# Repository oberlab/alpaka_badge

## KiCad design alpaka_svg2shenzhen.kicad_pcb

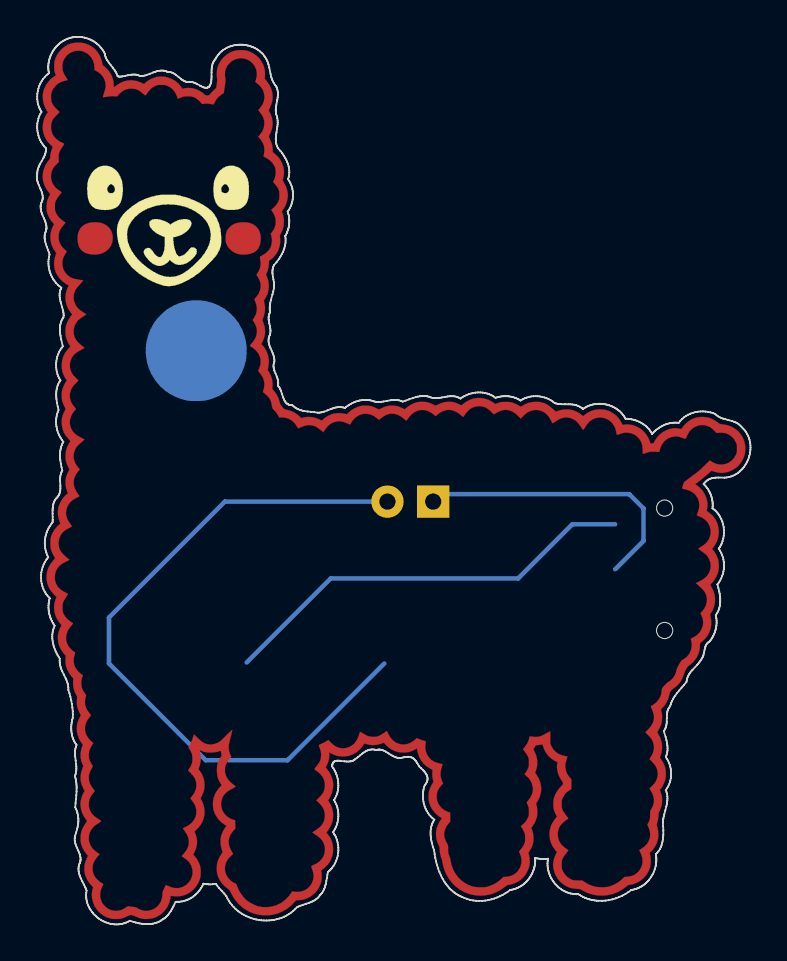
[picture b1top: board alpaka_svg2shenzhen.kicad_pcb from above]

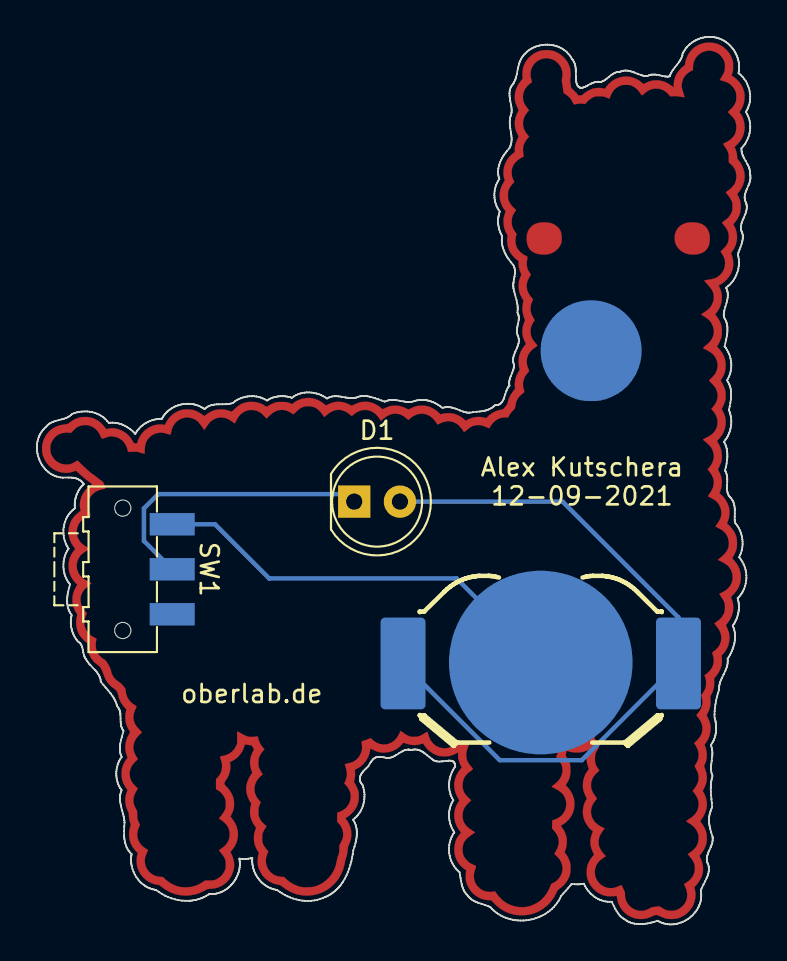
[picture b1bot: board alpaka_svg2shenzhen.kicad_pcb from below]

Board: 2 copper layers, 39.6 x 49.3 mm, 3 parts (3 on the bottom side), 3 nets.

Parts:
BT1: Battery_Cell; BAT-HLD-012-SMT
D1: LED; LED_D5.0mm
SW1: SW_DPDT_x2; SW_SPDT_CK-JS102011SAQN

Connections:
unnamed: BT1.2, BT1.3, D1.2
unnamed: BT1.1, SW1.1
unnamed: D1.1, SW1.2

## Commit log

2021-09-11 created first version of the PCB badge
2021-09-11 updated back silk text
2021-10-07 fixed wrong connections, increased size of pin pad
